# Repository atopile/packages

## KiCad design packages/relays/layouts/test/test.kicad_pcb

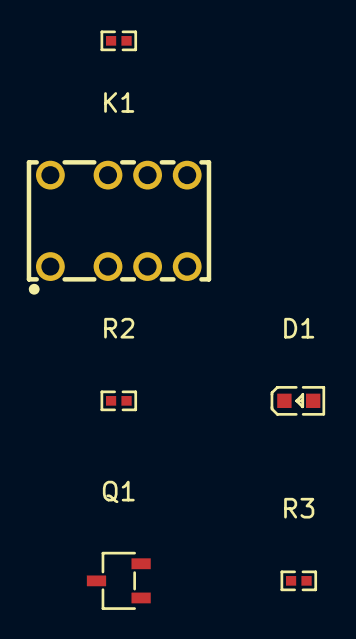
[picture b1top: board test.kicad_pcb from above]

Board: 2 copper layers, 6 parts (0 on the bottom side), 6 nets.

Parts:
D1: LED0603-RD
K1: RELAY-TH_HFDXXX
Q1: SOT-23-3_L2.9-W1.6-P1.90-LS2.8-BR
R1: 10kΩ ±1% 62.5mW; R0402
R2: 1kΩ ±1% 62.5mW; R0402
R3: 2kΩ ±1% 62.5mW; R0402

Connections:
-gnd-0: Q1.3, R2.2
-hv-0: D1.2, K1.1
cathode: D1.1, R3.1
gate: Q1.1, R1.2
line: R1.1, R2.1
power_relay-gnd: K1.8, Q1.2, R3.2

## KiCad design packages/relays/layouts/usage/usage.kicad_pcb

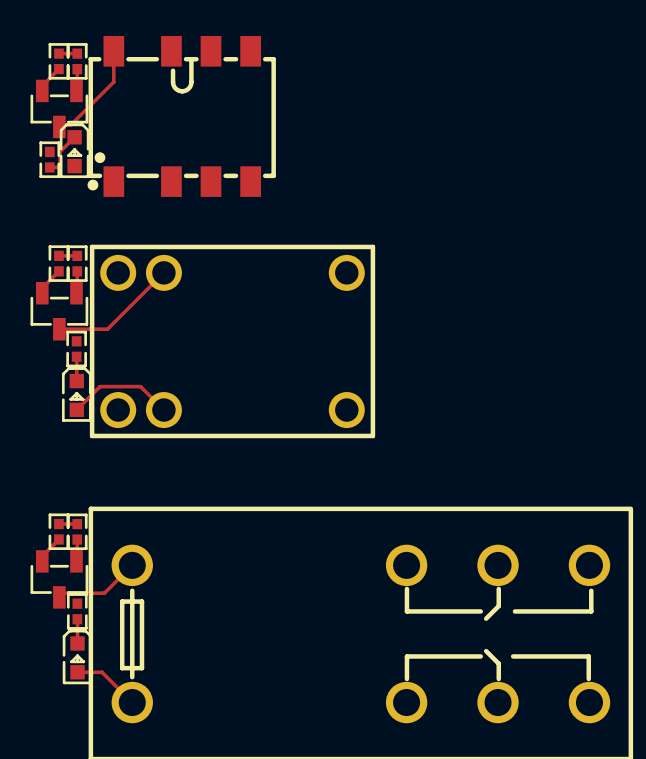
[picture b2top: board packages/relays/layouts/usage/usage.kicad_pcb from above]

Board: 2 copper layers, 18 parts (0 on the bottom side), 19 nets.

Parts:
K1: RELAY-TH_G2R-2-DCXX
K2: RELAY-TH_HK4100F-DC12V-SHG
LED1, LED2, LED3: LED0603-RD
Q1, Q2, Q3: SOT-23-3_L2.9-W1.3-P1.90-LS2.4-BR
R1, R2, R4, R5, R7, R8: 10000Ω; R0402
R3: 0Ω; R0402
R6: 4700Ω; R0402
R9: 20000Ω; R0402
U1: RELAY-SMD_G6K-2F-Y

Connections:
anode: LED1.2, U1.1
cathode: LED1.1, R3.1
contacts[1]: Q1.3, U1.8
gate: Q1.1, R2.2
input_electrical: K2.6, K2.7
line: R7.1, R8.1
lv: Q1.2, R1.2, R3.2
relay_DPDT_1A_3V-enable-line: R1.1, R2.1
relay_DPDT_5A_5V-coil_power-anode: K1.1, LED2.2
relay_DPDT_5A_5V-coil_power-lv: Q2.2, R4.2, R6.2
relay_DPDT_5A_5V-contacts[1]: K1.8, Q2.3
relay_DPDT_5A_5V-enable-line: R4.1, R5.1
relay_DPDT_5A_5V.coil_switch-gate: Q2.1, R5.2
relay_DPDT_5A_5V.indicator_led-cathode: LED2.1, R6.1
relay_SPDT_3A_12V-coil_power-anode: K2.2, LED3.2
relay_SPDT_3A_12V-coil_power-lv: Q3.2, R7.2, R9.2
relay_SPDT_3A_12V-contacts[1]: K2.11, Q3.3
relay_SPDT_3A_12V.coil_switch-gate: Q3.1, R8.2
relay_SPDT_3A_12V.indicator_led-cathode: LED3.1, R9.1

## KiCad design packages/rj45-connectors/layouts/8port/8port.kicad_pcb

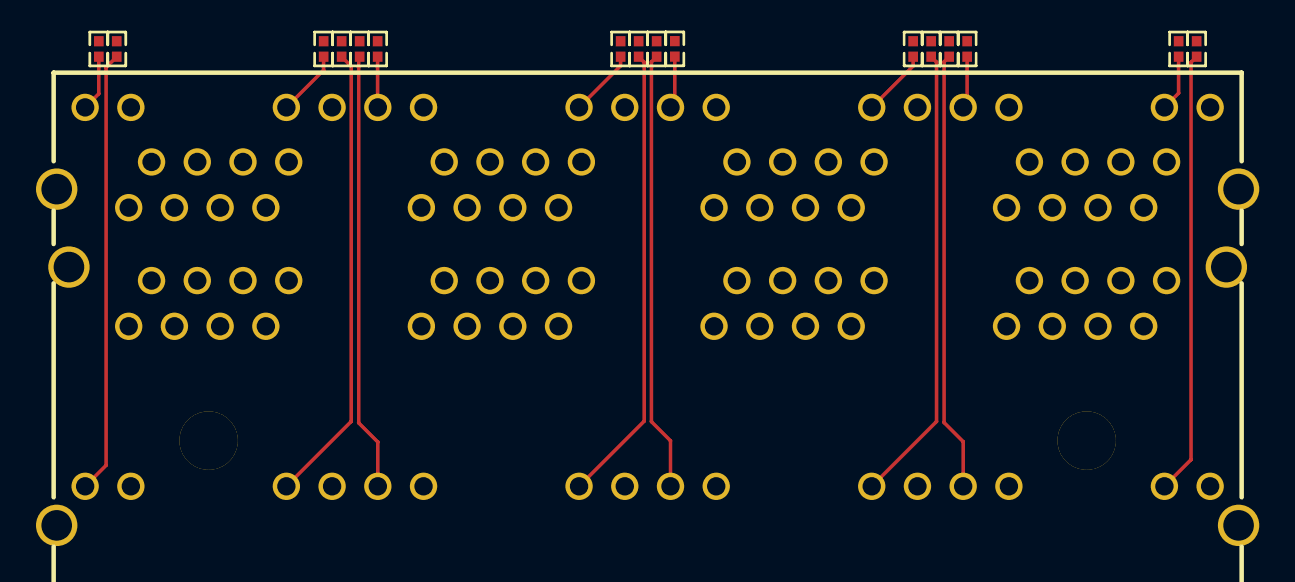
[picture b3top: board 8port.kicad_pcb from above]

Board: 2 copper layers, 17 parts (0 on the bottom side), 17 nets.

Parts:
R1, R2, R3, R4, R5, R6, R7, R8, R9, R10, R11, R12, R13, R14, R15, R16: 470Ω; R0402
U1: RJ45-TH_HC-RJ45-059C-2X4-1

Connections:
10: R9.2, U1.10
12: R1.2, U1.12
22: R10.2, U1.22
24: R2.2, U1.24
34: R11.2, U1.34
36: R3.2, U1.36
46: R12.2, U1.46
48: R4.2, U1.48
57: R5.2, U1.57
59: R13.2, U1.59
69: R6.2, U1.69
71: R14.2, U1.71
81: R7.2, U1.81
83: R15.2, U1.83
93: R8.2, U1.93
95: R16.2, U1.95
lv: U1.9, U1.11, U1.21, U1.23, U1.33, U1.35, U1.45, U1.47, U1.58, U1.60, U1.70, U1.72, U1.82, U1.84, U1.94, U1.96, U1.97, U1.98, U1.99, U1.100, U1.101, U1.102

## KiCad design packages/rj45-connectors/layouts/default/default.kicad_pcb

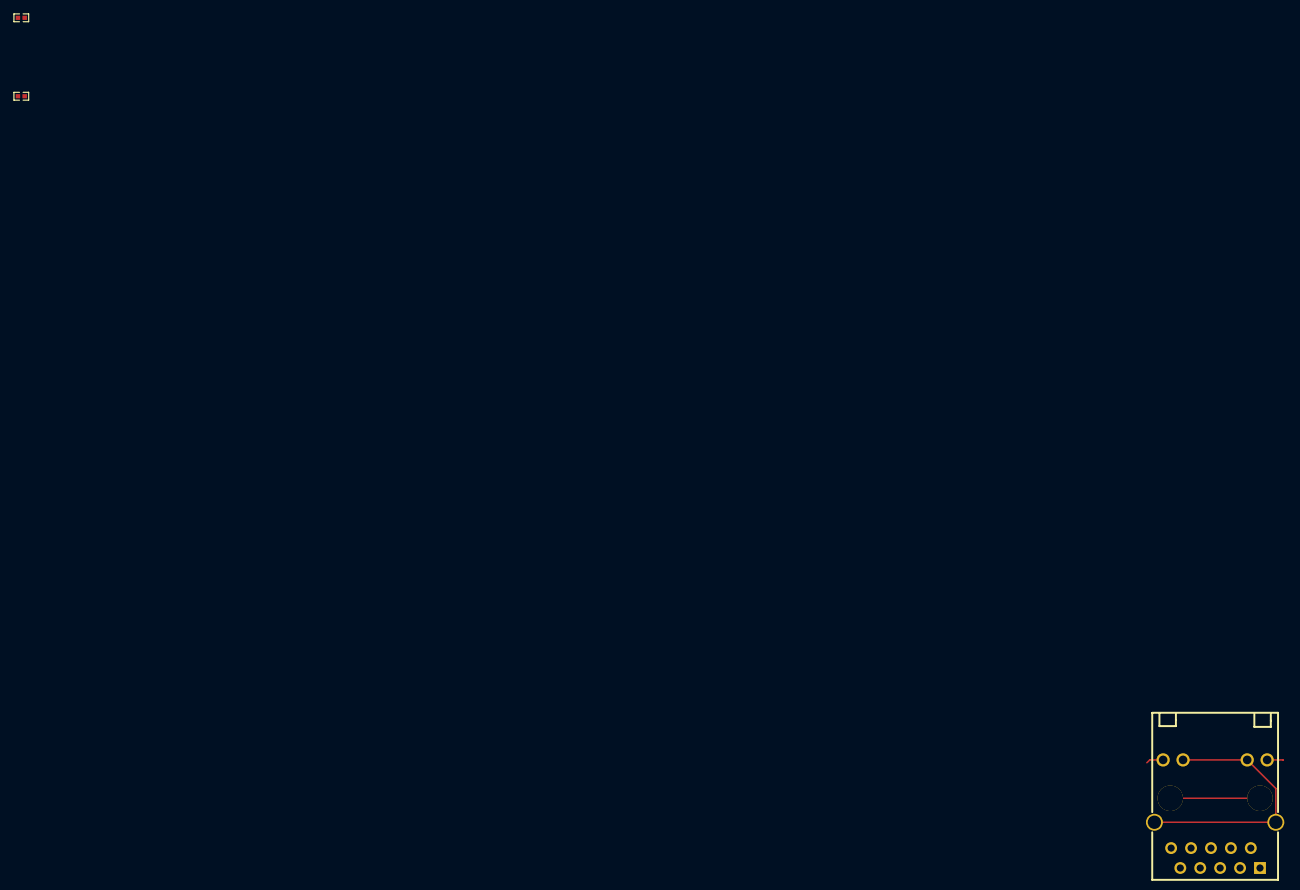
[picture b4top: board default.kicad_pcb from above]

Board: 2 copper layers, 3 parts (0 on the bottom side), 3 nets.

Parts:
R1, R2: 470±5.0%Ω; R0402
U1: RJ45-TH_HR911130A

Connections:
11: R2.2, U1.11
14: R1.2, U1.14
lv: U1.12, U1.13, U1.SHIELD0, U1.SHIELD1

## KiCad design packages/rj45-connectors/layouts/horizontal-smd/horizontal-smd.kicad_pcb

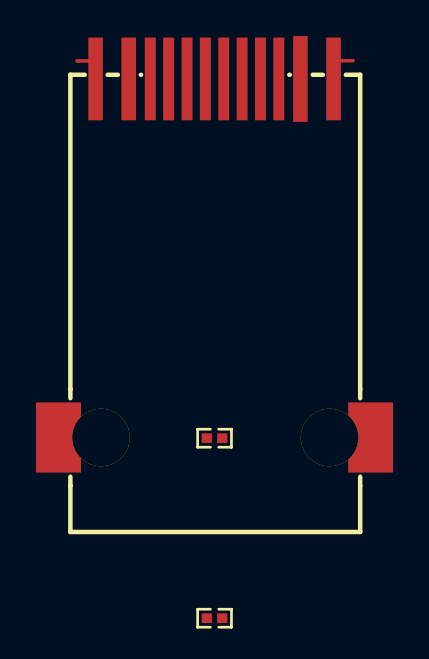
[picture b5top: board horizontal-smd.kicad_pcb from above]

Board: 2 copper layers, 3 parts (0 on the bottom side), 4 nets.

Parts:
R1, R2: 470Ω; R0402
RJ1: RJ45-SMD_BS-R250210

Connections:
CT: RJ1.3, RJ1.4
L_LED_Gpos: R2.2, RJ1.12
R_LEDYpos: R1.2, RJ1.9
lv: RJ1.8, RJ1.10, RJ1.11, RJ1.13, RJ1.14

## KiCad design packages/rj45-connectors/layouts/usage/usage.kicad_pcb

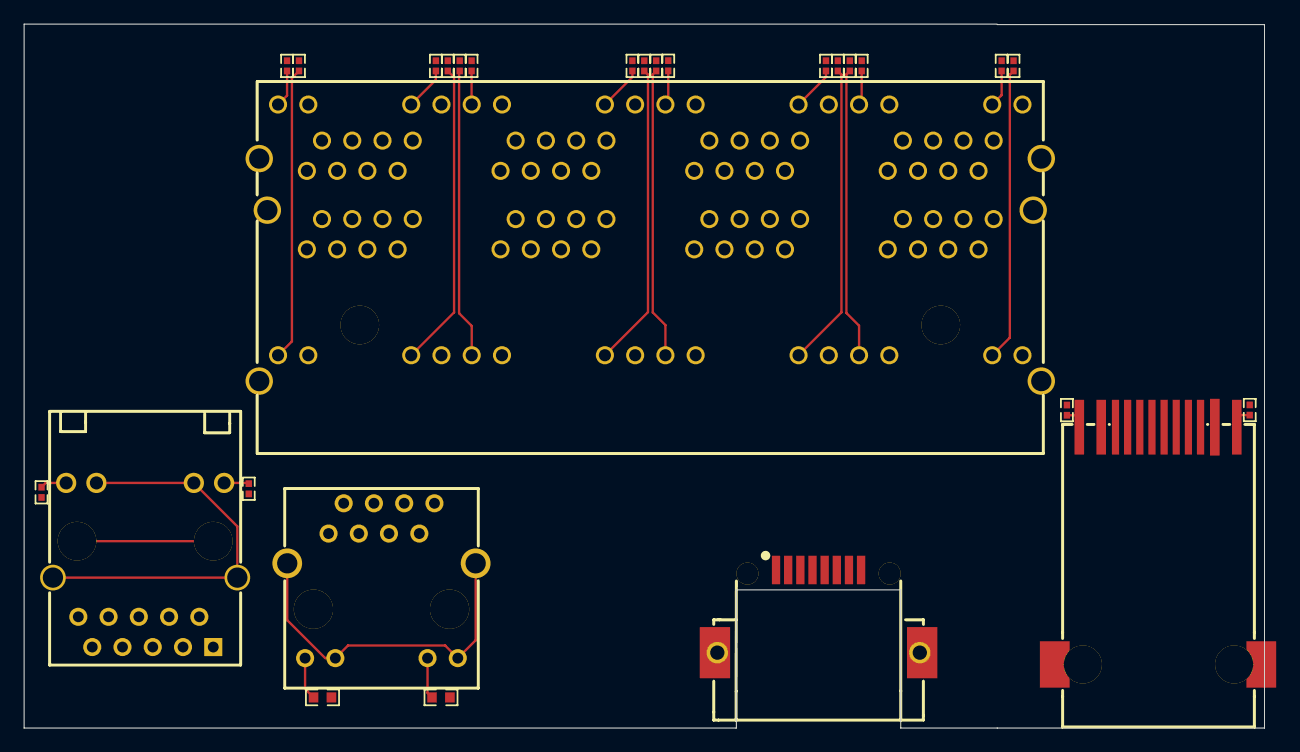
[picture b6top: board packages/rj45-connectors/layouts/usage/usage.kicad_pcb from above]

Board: 2 copper layers, 104.1 x 59.1 mm, 27 parts (0 on the bottom side), 24 nets.

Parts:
R1, R2, R5, R6, R7, R8, R9, R10, R11, R12, R13, R14, R15, R16, R17, R18, R19, R20, R21, R22: 470Ω; R0402
R3, R4: 10000Ω; R0603
RJ1: RJ45-TH_HR911130A
RJ2: RJ45-SMD_BS-R250210
U1: RJ45-TH_R-RJ45S08P-C000
U2: RJ45-SMD_HC-RJ45-055-7_1
U3: RJ45-TH_HC-RJ45-059C-2X4-1

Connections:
10: R13.2, U3.10
11: R2.2, RJ1.11
12: R5.2, U3.12
14: R1.2, RJ1.14
22: R14.2, U3.22
24: R6.2, U3.24
34: R15.2, U3.34
36: R7.2, U3.36
46: R16.2, U3.46
48: R8.2, U3.48
57: R9.2, U3.57
59: R17.2, U3.59
69: R10.2, U3.69
71: R18.2, U3.71
81: R11.2, U3.81
83: R19.2, U3.83
93: R12.2, U3.93
95: R20.2, U3.95
CT: RJ2.3, RJ2.4
Gpos: R4.2, U1.11
L_LED_Gpos: R22.2, RJ2.12
R_LEDYpos: R21.2, RJ2.9
Ypos: R3.2, U1.9
lv: RJ1.12, RJ1.13, RJ1.SHIELD0, RJ1.SHIELD1, RJ2.8, RJ2.10, RJ2.11, RJ2.13, RJ2.14, U1.10, U1.12, U1.13, U1.14, U2.9, U2.10, U3.9, U3.11, U3.21, U3.23, U3.33, U3.35, U3.45, U3.47, U3.58, U3.60, U3.70, U3.72, U3.82, U3.84, U3.94, U3.96, U3.97, U3.98, U3.99, U3.100, U3.101, U3.102
